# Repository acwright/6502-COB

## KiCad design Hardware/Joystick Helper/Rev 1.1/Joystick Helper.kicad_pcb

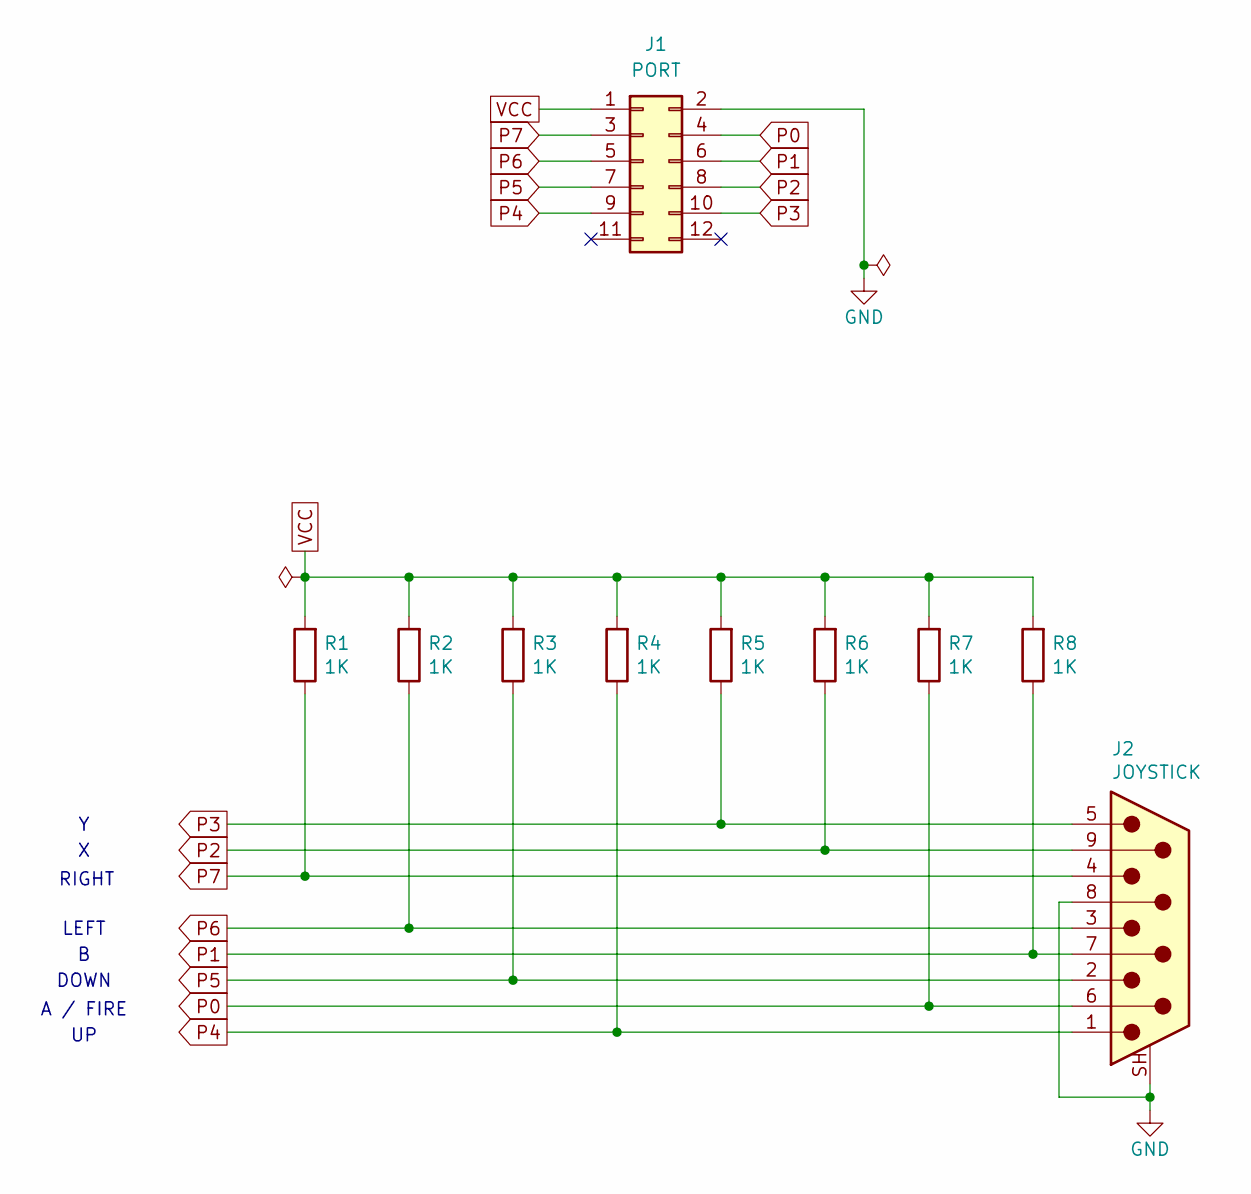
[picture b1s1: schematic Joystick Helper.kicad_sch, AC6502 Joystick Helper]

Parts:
J1: PORT; 6502 GPIO Connector; Digikey 2057-BHR-12-VUA-ND
J2: JOYSTICK; DSUB-9_Pins_Horizontal_P2.77x2.84mm_EdgePinOffset7.70mm_Hou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; Digikey 609-1481-ND
R1, R2, R3, R4, R5, R6, R7, R8: 1K; R_Axial_DIN0204_L3.6mm_D1.6mm_P5.08mm_Horizontal; Digikey 13-MFR-12FTF52-1KCT-ND

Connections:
GND: J1.2, J2.8, J2.SH (PAD)
P0: J1.4, J2.6, R7.1
P1: J1.6, J2.7, R8.1
P2: J1.8, J2.9, R6.1
P3: J1.10, J2.5, R5.1
P4: J1.9, J2.1, R4.1
P5: J1.7, J2.2, R3.1
P6: J1.5, J2.3, R2.1
P7: J1.3, J2.4, R1.1
VCC: J1.1, R1.2, R2.2, R3.2, R4.2, R5.2, R6.2, R7.2, R8.2

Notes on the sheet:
LEFT
DOWN
RIGHT
A / FIRE

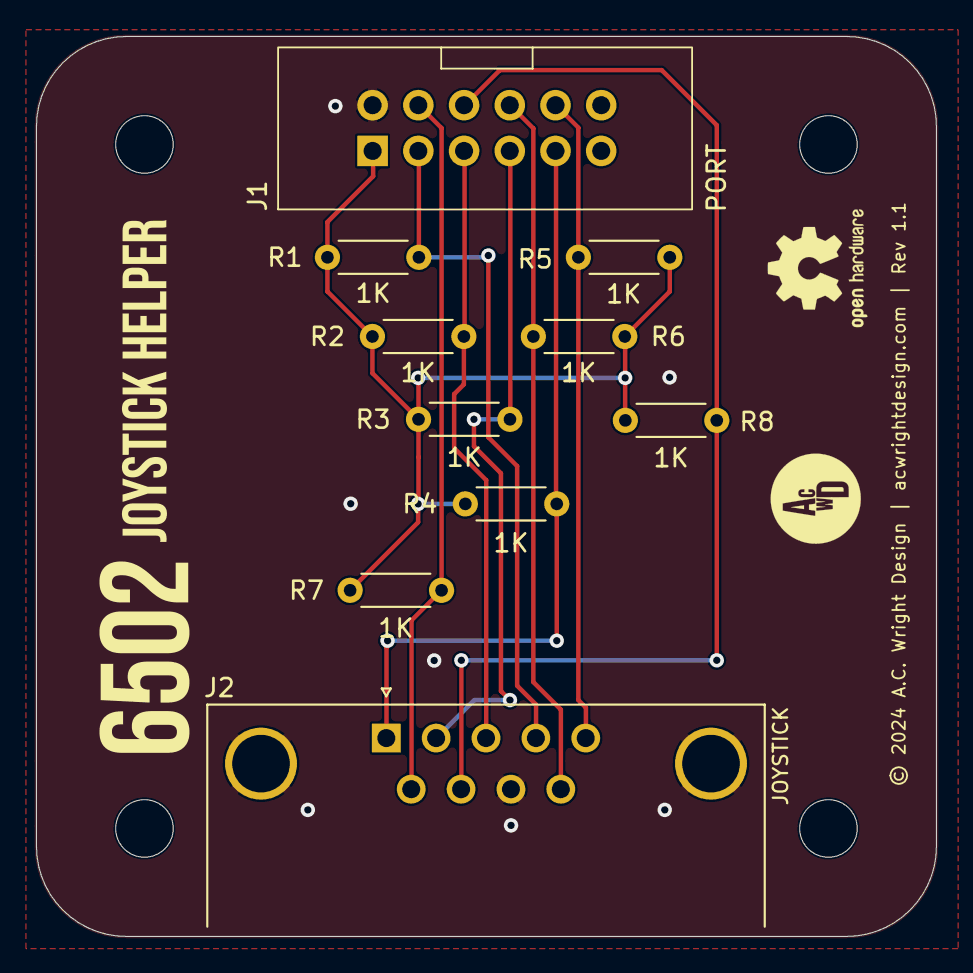
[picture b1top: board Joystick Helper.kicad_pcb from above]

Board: 2 copper layers, 50.0 x 50.0 mm, 14 parts (0 on the bottom side), 10 nets.

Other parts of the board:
H1, H2, H3, H4: MountingHole; MountingHole_3.2mm_M3

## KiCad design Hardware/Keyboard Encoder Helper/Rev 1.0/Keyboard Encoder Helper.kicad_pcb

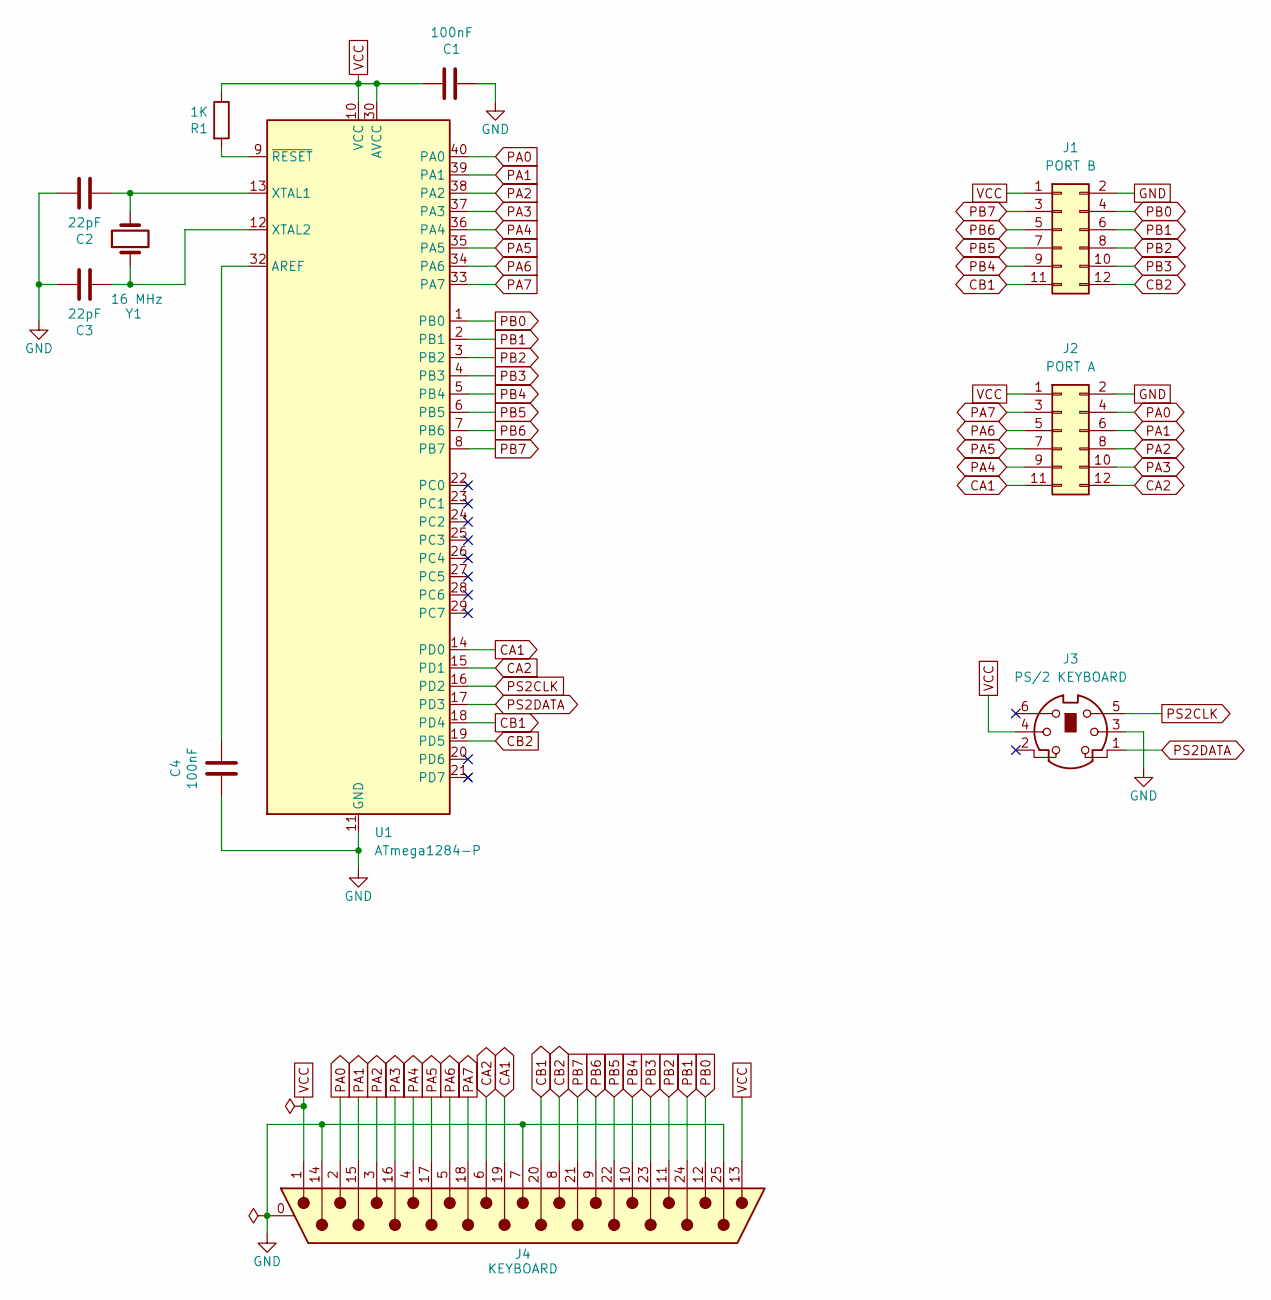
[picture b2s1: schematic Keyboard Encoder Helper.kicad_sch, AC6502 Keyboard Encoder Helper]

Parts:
C1, C4: 100nF; C_Disc_D5.0mm_W2.5mm_P2.50mm; Digikey 478-3187-ND
C2, C3: 22pF; C_Disc_D5.0mm_W2.5mm_P2.50mm; Digikey 478-4846-ND
J1: PORT B; 6502 GPIO Connector; Digikey 2057-BHR-12-VUA-ND
J2: PORT A; 6502 GPIO Connector; Digikey 2057-BHR-12-VUA-ND
J3: PS/2 KEYBOARD; PS2 Jack; Digikey 2092-KMDGX-6S-BS-ND
J4: KEYBOARD; DSUB-25_Pins_Horizontal_P2.77x2.84mm_EdgePinOffset7.70mm_Ho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; Digikey 609-1505-ND
R1: 1K; R_Axial_DIN0204_L3.6mm_D1.6mm_P5.08mm_Horizontal; Digikey 13-MFR-12FTF52-1KCT-ND
U1: ATmega1284-P; DIP-40_W15.24mm_Socket_LongPads; Digikey ATMEGA1284-PU-ND
Y1: 16 MHz; Crystal_HC49-U_Vertical; Digikey X1103-ND

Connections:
CA1: J2.11, J4.19, U1.14 (PD0)
CA2: J2.12, J4.6, U1.15 (PD1)
CB1: J1.11, J4.20, U1.18 (PD4)
CB2: J1.12, J4.8, U1.19 (PD5)
GND: C1.1, C2.2, C3.2, C4.1, J1.2, J2.2, J3.3, J4.0 (PAD), J4.7, J4.14, J4.25, U1.11 (GND), U1.31 (GND)
unnamed: C4.2, U1.32 (AREF)
unnamed: C2.1, U1.13 (XTAL1), Y1.2
unnamed: C3.1, U1.12 (XTAL2), Y1.1
unnamed: R1.2, U1.9 (~RESET)
PA0: J2.4, J4.2, U1.40 (PA0)
PA1: J2.6, J4.15, U1.39 (PA1)
PA2: J2.8, J4.3, U1.38 (PA2)
PA3: J2.10, J4.16, U1.37 (PA3)
PA4: J2.9, J4.4, U1.36 (PA4)
PA5: J2.7, J4.17, U1.35 (PA5)
PA6: J2.5, J4.5, U1.34 (PA6)
PA7: J2.3, J4.18, U1.33 (PA7)
PB0: J1.4, J4.12, U1.1 (PB0)
PB1: J1.6, J4.24, U1.2 (PB1)
PB2: J1.8, J4.11, U1.3 (PB2)
PB3: J1.10, J4.23, U1.4 (PB3)
PB4: J1.9, J4.10, U1.5 (PB4)
PB5: J1.7, J4.22, U1.6 (PB5)
PB6: J1.5, J4.9, U1.7 (PB6)
PB7: J1.3, J4.21, U1.8 (PB7)
PS2CLK: J3.5, U1.16 (PD2)
PS2DATA: J3.1, U1.17 (PD3)
VCC: C1.2, J1.1, J2.1, J3.4, J4.1, J4.13, R1.1, U1.10 (VCC), U1.30 (AVCC)

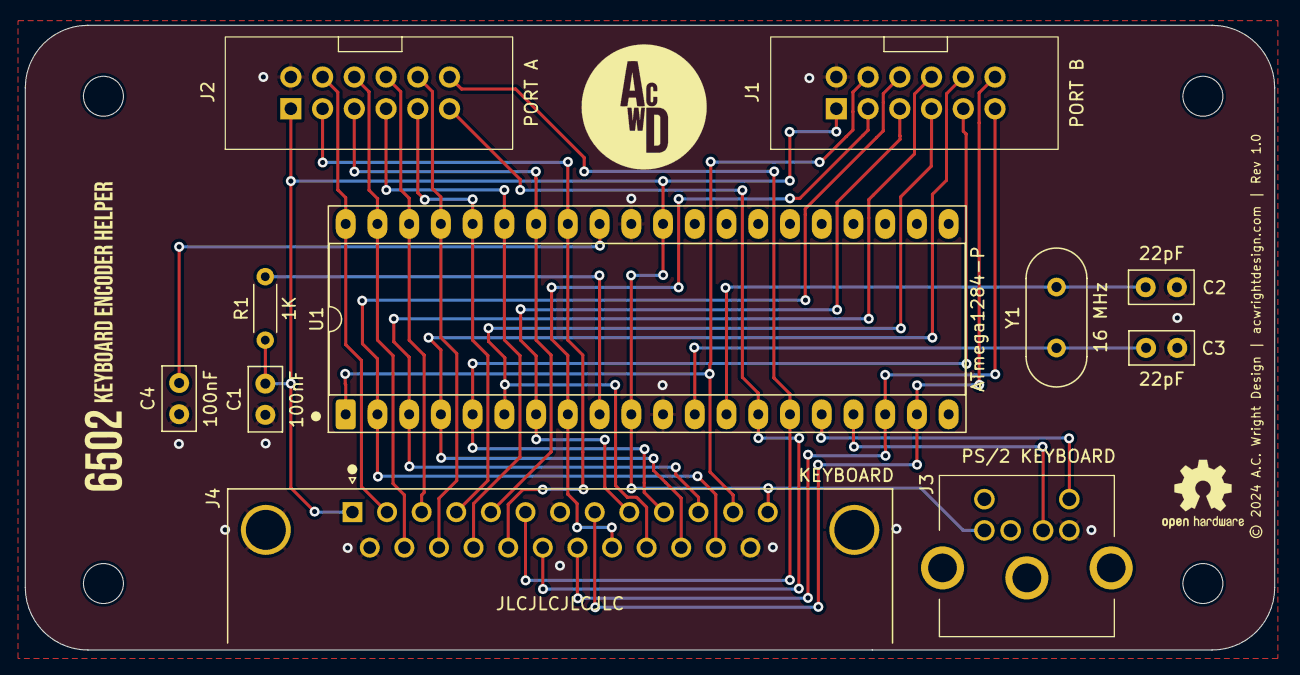
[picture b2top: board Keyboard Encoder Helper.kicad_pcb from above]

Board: 2 copper layers, 100.0 x 50.0 mm, 15 parts (0 on the bottom side), 28 nets.

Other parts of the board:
H1, H2, H3, H4: MountingHole; MountingHole_3.2mm_M3

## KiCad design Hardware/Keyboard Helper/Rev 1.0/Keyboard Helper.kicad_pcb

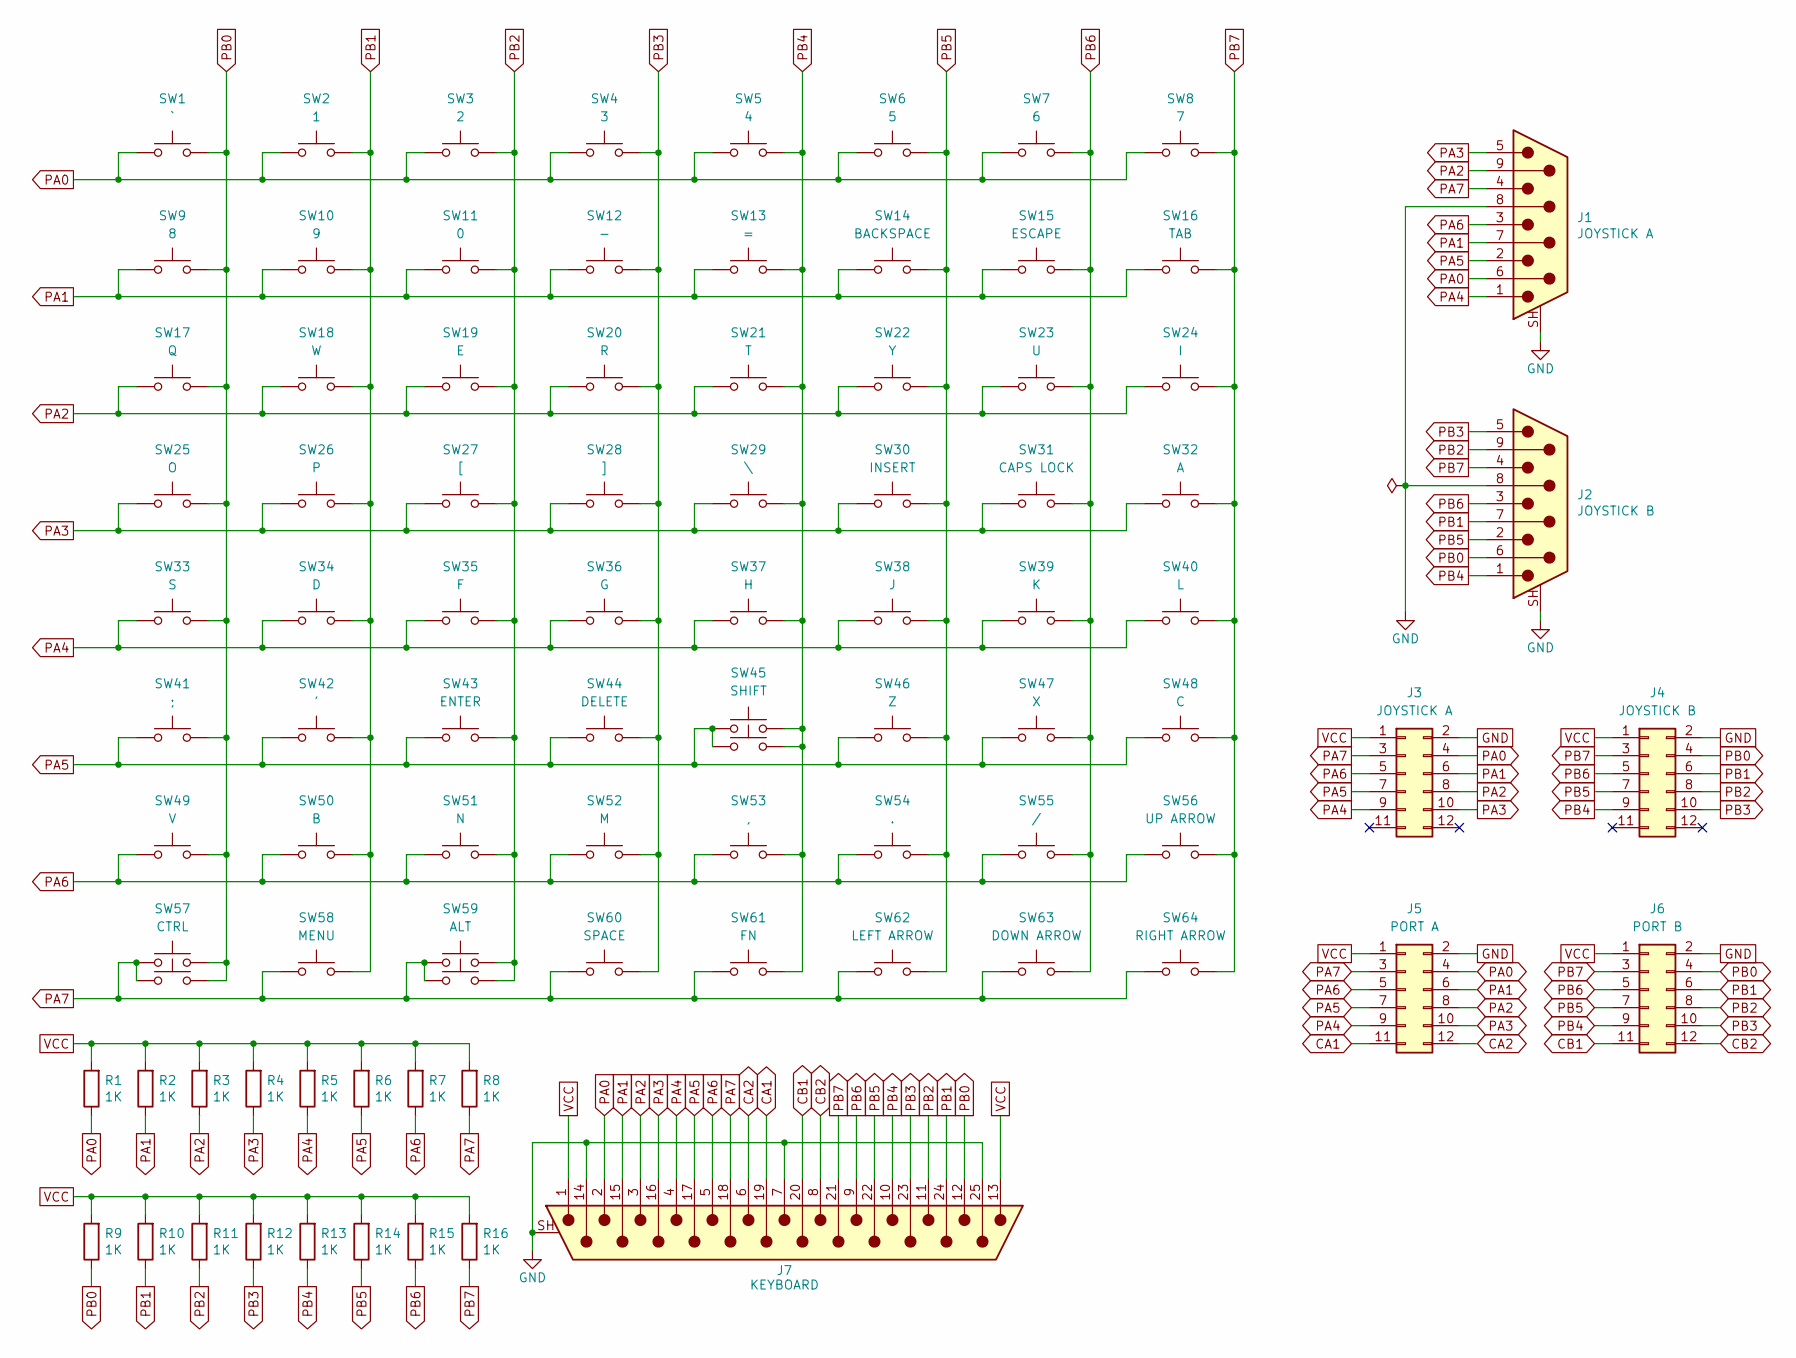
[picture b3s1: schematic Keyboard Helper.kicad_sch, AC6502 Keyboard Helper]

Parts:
J1: JOYSTICK A; DSUB-9_Pins_Horizontal_P2.77x2.84mm_EdgePinOffset7.70mm_Hou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; Digikey 609-1481-ND
J2: JOYSTICK B; DSUB-9_Pins_Horizontal_P2.77x2.84mm_EdgePinOffset7.70mm_Hou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; Digikey 609-1481-ND
J3: JOYSTICK A; 6502 GPIO Connector; Digikey 2057-BHR-12-VUA-ND
J4: JOYSTICK B; 6502 GPIO Connector; Digikey 2057-BHR-12-VUA-ND
J5: PORT A; 6502 GPIO Connector; Digikey 2057-BHR-12-VUA-ND
J6: PORT B; 6502 GPIO Connector; Digikey 2057-BHR-12-VUA-ND
J7: KEYBOARD; DSUB-25_Pins_Horizontal_P2.77x2.84mm_EdgePinOffset7.70mm_Ho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; Digikey 609-1505-ND
R1, R2, R3, R4, R5, R6, R7, R8, R9, R10, R11, R12, R13, R14, R15, R16: 1K; R_Axial_DIN0204_L3.6mm_D1.6mm_P5.08mm_Horizontal; Digikey 13-MFR-12FTF52-1KCT-ND
SW1: `; SW_Cherry_MX_1.00u_PCB; Digikey 1644-MX2A-E1NA-ND
SW2: 1; SW_Cherry_MX_1.00u_PCB; Digikey 1644-MX2A-E1NA-ND
SW3: 2; SW_Cherry_MX_1.00u_PCB; Digikey 1644-MX2A-E1NA-ND
SW4: 3; SW_Cherry_MX_1.00u_PCB; Digikey 1644-MX2A-E1NA-ND
SW5: 4; SW_Cherry_MX_1.00u_PCB; Digikey 1644-MX2A-E1NA-ND
SW6: 5; SW_Cherry_MX_1.00u_PCB; Digikey 1644-MX2A-E1NA-ND
SW7: 6; SW_Cherry_MX_1.00u_PCB; Digikey 1644-MX2A-E1NA-ND
SW8: 7; SW_Cherry_MX_1.00u_PCB; Digikey 1644-MX2A-E1NA-ND
SW9: 8; SW_Cherry_MX_1.00u_PCB; Digikey 1644-MX2A-E1NA-ND
SW10: 9; SW_Cherry_MX_1.00u_PCB; Digikey 1644-MX2A-E1NA-ND
SW11: 0; SW_Cherry_MX_1.00u_PCB; Digikey 1644-MX2A-E1NA-ND
SW12: -; SW_Cherry_MX_1.00u_PCB; Digikey 1644-MX2A-E1NA-ND
SW13: =; SW_Cherry_MX_1.00u_PCB; Digikey 1644-MX2A-E1NA-ND
SW14: BACKSPACE; SW_Cherry_MX_2.00u_PCB; Digikey 1644-MX2A-E1NA-ND
SW15: ESCAPE; SW_Cherry_MX_1.00u_PCB; Digikey 1644-MX2A-E1NA-ND
SW16: TAB; SW_Cherry_MX_1.50u_PCB; Digikey 1644-MX2A-E1NA-ND
SW17: Q; SW_Cherry_MX_1.00u_PCB; Digikey 1644-MX2A-E1NA-ND
SW18: W; SW_Cherry_MX_1.00u_PCB; Digikey 1644-MX2A-E1NA-ND
SW19: E; SW_Cherry_MX_1.00u_PCB; Digikey 1644-MX2A-E1NA-ND
SW20: R; SW_Cherry_MX_1.00u_PCB; Digikey 1644-MX2A-E1NA-ND
SW21: T; SW_Cherry_MX_1.00u_PCB; Digikey 1644-MX2A-E1NA-ND
SW22: Y; SW_Cherry_MX_1.00u_PCB; Digikey 1644-MX2A-E1NA-ND
SW23: U; SW_Cherry_MX_1.00u_PCB; Digikey 1644-MX2A-E1NA-ND
SW24: I; SW_Cherry_MX_1.00u_PCB; Digikey 1644-MX2A-E1NA-ND
SW25: O; SW_Cherry_MX_1.00u_PCB; Digikey 1644-MX2A-E1NA-ND
SW26: P; SW_Cherry_MX_1.00u_PCB; Digikey 1644-MX2A-E1NA-ND
SW27: [; SW_Cherry_MX_1.00u_PCB; Digikey 1644-MX2A-E1NA-ND
SW28: ]; SW_Cherry_MX_1.00u_PCB; Digikey 1644-MX2A-E1NA-ND
SW29: \; SW_Cherry_MX_1.50u_PCB; Digikey 1644-MX2A-E1NA-ND
SW30: INSERT; SW_Cherry_MX_1.00u_PCB; Digikey 1644-MX2A-E1NA-ND
SW31: CAPS LOCK; SW_Cherry_MX_1.75u_PCB; Digikey 1644-MX2A-E1NA-ND
SW32: A; SW_Cherry_MX_1.00u_PCB; Digikey 1644-MX2A-E1NA-ND
SW33: S; SW_Cherry_MX_1.00u_PCB; Digikey 1644-MX2A-E1NA-ND
SW34: D; SW_Cherry_MX_1.00u_PCB; Digikey 1644-MX2A-E1NA-ND
SW35: F; SW_Cherry_MX_1.00u_PCB; Digikey 1644-MX2A-E1NA-ND
SW36: G; SW_Cherry_MX_1.00u_PCB; Digikey 1644-MX2A-E1NA-ND
SW37: H; SW_Cherry_MX_1.00u_PCB; Digikey 1644-MX2A-E1NA-ND
SW38: J; SW_Cherry_MX_1.00u_PCB; Digikey 1644-MX2A-E1NA-ND
SW39: K; SW_Cherry_MX_1.00u_PCB; Digikey 1644-MX2A-E1NA-ND
SW40: L; SW_Cherry_MX_1.00u_PCB; Digikey 1644-MX2A-E1NA-ND
SW41: ;; SW_Cherry_MX_1.00u_PCB; Digikey 1644-MX2A-E1NA-ND
SW42: '; SW_Cherry_MX_1.00u_PCB; Digikey 1644-MX2A-E1NA-ND
SW43: ENTER; SW_Cherry_MX_2.25u_PCB; Digikey 1644-MX2A-E1NA-ND
SW44: DELETE; SW_Cherry_MX_1.00u_PCB; Digikey 1644-MX2A-E1NA-ND
SW45: SHIFT; SW_Cherry_MX_2.25u_PCB; Digikey 1644-MX2A-E1NA-ND
SW46: Z; SW_Cherry_MX_1.00u_PCB; Digikey 1644-MX2A-E1NA-ND
SW47: X; SW_Cherry_MX_1.00u_PCB; Digikey 1644-MX2A-E1NA-ND
SW48: C; SW_Cherry_MX_1.00u_PCB; Digikey 1644-MX2A-E1NA-ND
SW49: V; SW_Cherry_MX_1.00u_PCB; Digikey 1644-MX2A-E1NA-ND
SW50: B; SW_Cherry_MX_1.00u_PCB; Digikey 1644-MX2A-E1NA-ND
SW51: N; SW_Cherry_MX_1.00u_PCB; Digikey 1644-MX2A-E1NA-ND
SW52: M; SW_Cherry_MX_1.00u_PCB; Digikey 1644-MX2A-E1NA-ND
SW53: ,; SW_Cherry_MX_1.00u_PCB; Digikey 1644-MX2A-E1NA-ND
SW54: .; SW_Cherry_MX_1.00u_PCB; Digikey 1644-MX2A-E1NA-ND
SW55: /; SW_Cherry_MX_1.00u_PCB; Digikey 1644-MX2A-E1NA-ND
SW56: UP ARROW; SW_Cherry_MX_1.00u_PCB; Digikey 1644-MX2A-E1NA-ND
SW57: CTRL; SW_Cherry_MX_1.25u_PCB; Digikey 1644-MX2A-E1NA-ND
SW58: MENU; SW_Cherry_MX_1.00u_PCB; Digikey 1644-MX2A-E1NA-ND
SW59: ALT; SW_Cherry_MX_1.25u_PCB; Digikey 1644-MX2A-E1NA-ND
SW60: SPACE; SW_Cherry_MX_6.25u_PCB; Digikey 1644-MX2A-E1NA-ND
SW61: FN; SW_Cherry_MX_1.25u_PCB; Digikey 1644-MX2A-E1NA-ND
SW62: LEFT ARROW; SW_Cherry_MX_1.00u_PCB; Digikey 1644-MX2A-E1NA-ND
SW63: DOWN ARROW; SW_Cherry_MX_1.00u_PCB; Digikey 1644-MX2A-E1NA-ND
SW64: RIGHT ARROW; SW_Cherry_MX_1.00u_PCB; Digikey 1644-MX2A-E1NA-ND
SW65: R SHIFT; SW_Cherry_MX_2.25u_PCB; Digikey 1644-MX2A-E1NA-ND
SW66: R ALT; SW_Cherry_MX_1.25u_PCB; Digikey 1644-MX2A-E1NA-ND
SW67: R CTRL; SW_Cherry_MX_1.25u_PCB; Digikey 1644-MX2A-E1NA-ND

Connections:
CA1: J5.11, J7.19
CA2: J5.12, J7.6
CB1: J6.11, J7.20
CB2: J6.12, J7.8
GND: J1.8, J1.SH (PAD), J2.8, J2.SH (PAD), J3.2, J4.2, J5.2, J6.2, J7.7, J7.14, J7.25, J7.SH (PAD)
PA0: J1.6, J3.4, J5.4, J7.2, R1.1, SW1.1, SW2.1, SW3.1, SW4.1, SW5.1, SW6.1, SW7.1, SW8.1
PA1: J1.7, J3.6, J5.6, J7.15, R2.1, SW9.1, SW10.1, SW11.1, SW12.1, SW13.1, SW14.1, SW15.1, SW16.1
PA2: J1.9, J3.8, J5.8, J7.3, R3.1, SW17.1, SW18.1, SW19.1, SW20.1, SW21.1, SW22.1, SW23.1, SW24.1
PA3: J1.5, J3.10, J5.10, J7.16, R4.1, SW25.1, SW26.1, SW27.1, SW28.1, SW29.1, SW30.1, SW31.1, SW32.1
PA4: J1.1, J3.9, J5.9, J7.4, R5.1, SW33.1, SW34.1, SW35.1, SW36.1, SW37.1, SW38.1, SW39.1, SW40.1
PA5: J1.2, J3.7, J5.7, J7.17, R6.1, SW41.1, SW42.1, SW43.1, SW44.1, SW45.1, SW46.1, SW47.1, SW48.1, SW65.1
PA6: J1.3, J3.5, J5.5, J7.5, R7.1, SW49.1, SW50.1, SW51.1, SW52.1, SW53.1, SW54.1, SW55.1, SW56.1
PA7: J1.4, J3.3, J5.3, J7.18, R8.1, SW57.1, SW58.1, SW59.1, SW60.1, SW61.1, SW62.1, SW63.1, SW64.1, SW66.1, SW67.1
PB0: J2.6, J4.4, J6.4, J7.12, R9.1, SW1.2, SW9.2, SW17.2, SW25.2, SW33.2, SW41.2, SW49.2, SW57.2, SW67.2
PB1: J2.7, J4.6, J6.6, J7.24, R10.1, SW2.2, SW10.2, SW18.2, SW26.2, SW34.2, SW42.2, SW50.2, SW58.2
PB2: J2.9, J4.8, J6.8, J7.11, R11.1, SW3.2, SW11.2, SW19.2, SW27.2, SW35.2, SW43.2, SW51.2, SW59.2, SW66.2
PB3: J2.5, J4.10, J6.10, J7.23, R12.1, SW4.2, SW12.2, SW20.2, SW28.2, SW36.2, SW44.2, SW52.2, SW60.2
PB4: J2.1, J4.9, J6.9, J7.10, R13.1, SW5.2, SW13.2, SW21.2, SW29.2, SW37.2, SW45.2, SW53.2, SW61.2, SW65.2
PB5: J2.2, J4.7, J6.7, J7.22, R14.1, SW6.2, SW14.2, SW22.2, SW30.2, SW38.2, SW46.2, SW54.2, SW62.2
PB6: J2.3, J4.5, J6.5, J7.9, R15.1, SW7.2, SW15.2, SW23.2, SW31.2, SW39.2, SW47.2, SW55.2, SW63.2
PB7: J2.4, J4.3, J6.3, J7.21, R16.1, SW8.2, SW16.2, SW24.2, SW32.2, SW40.2, SW48.2, SW56.2, SW64.2
VCC: J3.1, J4.1, J5.1, J6.1, J7.1, J7.13, R1.2, R2.2, R3.2, R4.2, R5.2, R6.2, R7.2, R8.2, R9.2, R10.2, R11.2, R12.2, R13.2, R14.2, R15.2, R16.2

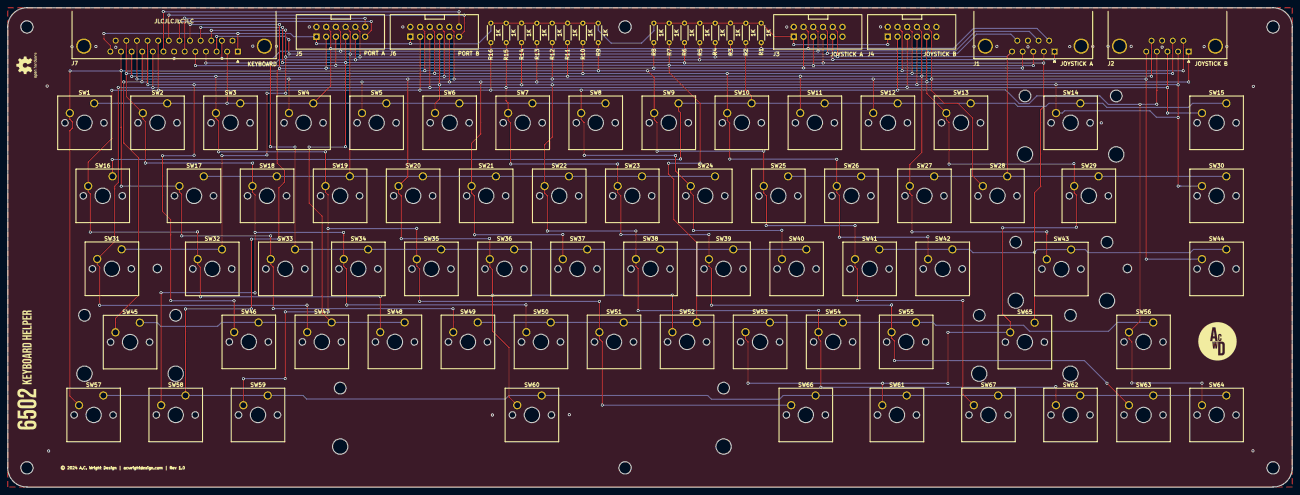
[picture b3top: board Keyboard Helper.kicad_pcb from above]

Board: 2 copper layers, 335.0 x 125.0 mm, 98 parts (0 on the bottom side), 22 nets.

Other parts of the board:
H1, H2, H2#2, H2#3, H3#3, H4: MountingHole; MountingHole_3.2mm_M3
H3, H3#2: MountingHole; MountingHole_2.2mm_M2

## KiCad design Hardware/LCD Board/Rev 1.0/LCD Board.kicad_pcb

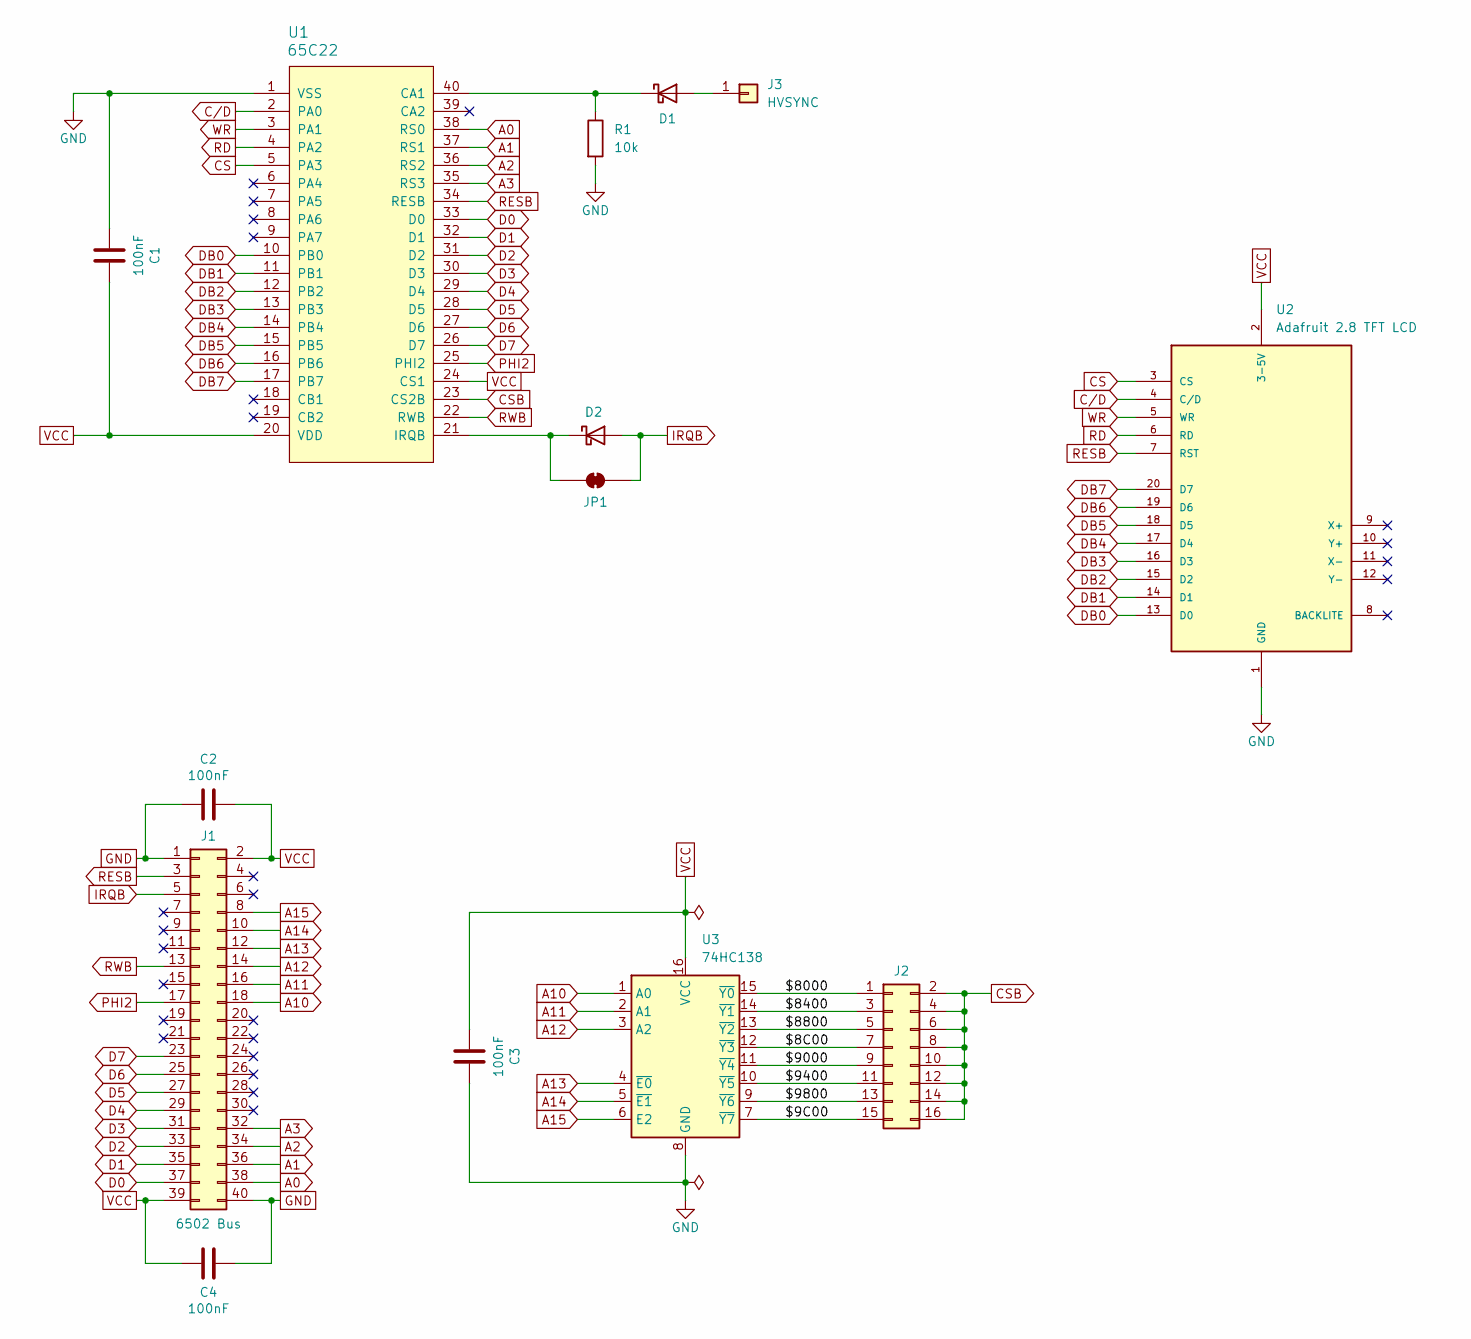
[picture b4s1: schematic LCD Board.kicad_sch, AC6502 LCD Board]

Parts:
C1, C2, C3, C4: 100nF; C_Disc_D5.0mm_W2.5mm_P2.50mm; Digikey 478-3187-ND
D1, D2: BAT85; D_DO-35_SOD27_P7.62mm_Horizontal; Digikey BAT85SCT-ND
J1: 6502 Bus; 6502 Bus Connector; Digikey 732-5401-ND
J2: Conn_02x08_Odd_Even; PinHeader_2x08_P2.54mm_Vertical; Digikey S2011EC-40-ND
J3: HVSYNC; PinHeader_1x01_P2.54mm_Vertical; Digikey S1011EC-40-ND
JP1: SolderJumper_2_Bridged; SolderJumper-2_P1.3mm_Bridged_RoundedPad1.0x1.5mm
R1: 10k; R_Axial_DIN0204_L3.6mm_D1.6mm_P5.08mm_Horizontal; Digikey 13-MFR-12FTF52-10KCT-ND
U1: 65C22; DIP-40_W15.24mm_Socket_LongPads; Mouser 955-W65C22N6TPG-14
U2: Adafruit 2.8 TFT LCD
U3: 74HC138; DIP-16_W7.62mm_Socket_LongPads; Digikey 296-1575-5-ND

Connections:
/$8C00: J2.7, U3.12 (~Y3)
/$9C00: J2.15, U3.7 (~Y7)
/$8000: J2.1, U3.15 (~Y0)
/$8400: J2.3, U3.14 (~Y1)
/$8800: J2.5, U3.13 (~Y2)
/$9000: J2.9, U3.11 (~Y4)
/$9400: J2.11, U3.10 (~Y5)
/$9800: J2.13, U3.9 (~Y6)
A0: J1.38, U1.38 (RS0)
A1: J1.36, U1.37 (RS1)
A2: J1.34, U1.36 (RS2)
A3: J1.32, U1.35 (RS3)
A10: J1.18, U3.1 (A0)
A11: J1.16, U3.2 (A1)
A12: J1.14, U3.3 (A2)
A13: J1.12, U3.4 (~E0)
A14: J1.10, U3.5 (~E1)
A15: J1.8, U3.6 (E2)
CS: U1.5 (PA3), U2.3 (CS)
CSB: J2.2, J2.4, J2.6, J2.8, J2.10, J2.12, J2.14, J2.16, U1.23 (CS2B)
C/D: U1.2 (PA0), U2.4 (C/D)
D0: J1.37, U1.33 (D0)
D1: J1.35, U1.32 (D1)
D2: J1.33, U1.31 (D2)
D3: J1.31, U1.30 (D3)
D4: J1.29, U1.29 (D4)
D5: J1.27, U1.28 (D5)
D6: J1.25, U1.27 (D6)
D7: J1.23, U1.26 (D7)
DB0: U1.10 (PB0), U2.13 (D0)
DB1: U1.11 (PB1), U2.14 (D1)
DB2: U1.12 (PB2), U2.15 (D2)
DB3: U1.13 (PB3), U2.16 (D3)
DB4: U1.14 (PB4), U2.17 (D4)
DB5: U1.15 (PB5), U2.18 (D5)
DB6: U1.16 (PB6), U2.19 (D6)
DB7: U1.17 (PB7), U2.20 (D7)
GND: C1.1, C2.2, C3.2, C4.1, J1.1, J1.40, R1.2, U1.1 (VSS), U2.1 (GND), U3.8 (GND)
IRQB: D2.2 (A), J1.5, JP1.2 (B)
unnamed: D1.2 (A), J3.1
unnamed: D1.1 (K), R1.1, U1.40 (CA1)
unnamed: D2.1 (K), JP1.1 (A), U1.21 (IRQB)
PHI2: J1.17, U1.25 (PHI2)
RD: U1.4 (PA2), U2.6 (RD)
RESB: J1.3, U1.34 (RESB), U2.7 (RST)
RWB: J1.13, U1.22 (RWB)
VCC: C1.2, C2.1, C3.1, C4.2, J1.2, J1.39, U1.20 (VDD), U1.24 (CS1), U2.2 (3-5V), U3.16 (VCC)
WR: U1.3 (PA1), U2.5 (WR)

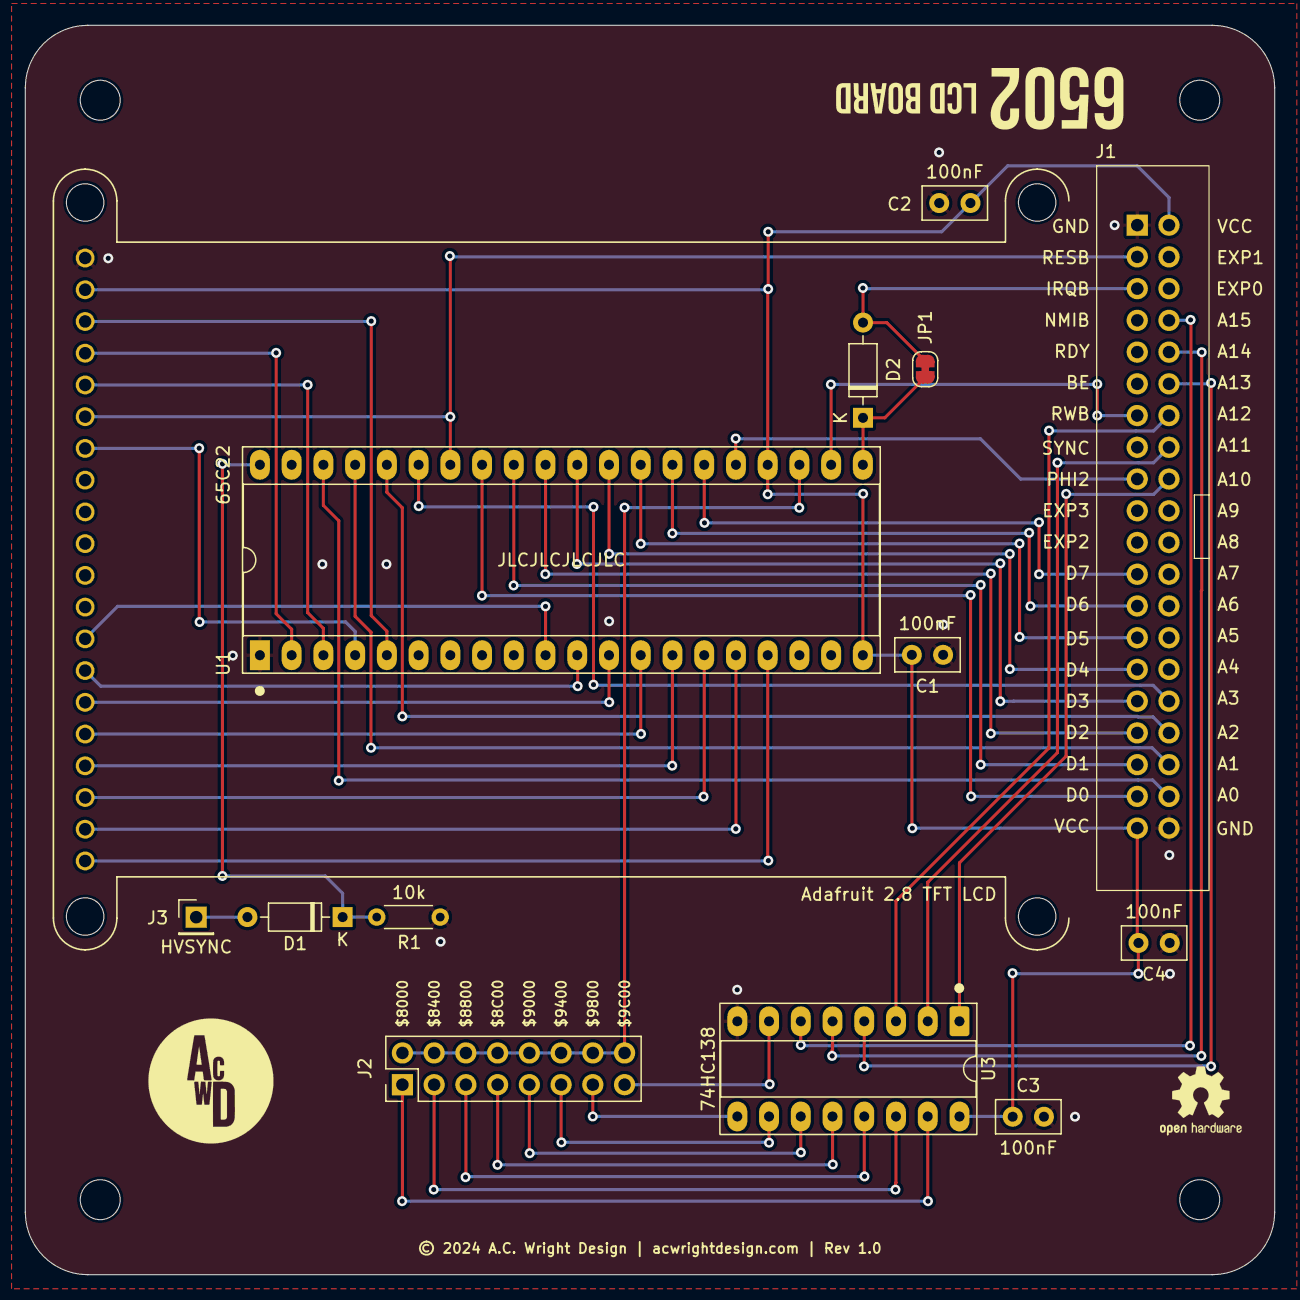
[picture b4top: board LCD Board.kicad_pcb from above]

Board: 2 copper layers, 100.0 x 100.0 mm, 18 parts (0 on the bottom side), 48 nets.

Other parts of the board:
H1, H2, H3, H4: MountingHole; MountingHole_3.2mm_M3

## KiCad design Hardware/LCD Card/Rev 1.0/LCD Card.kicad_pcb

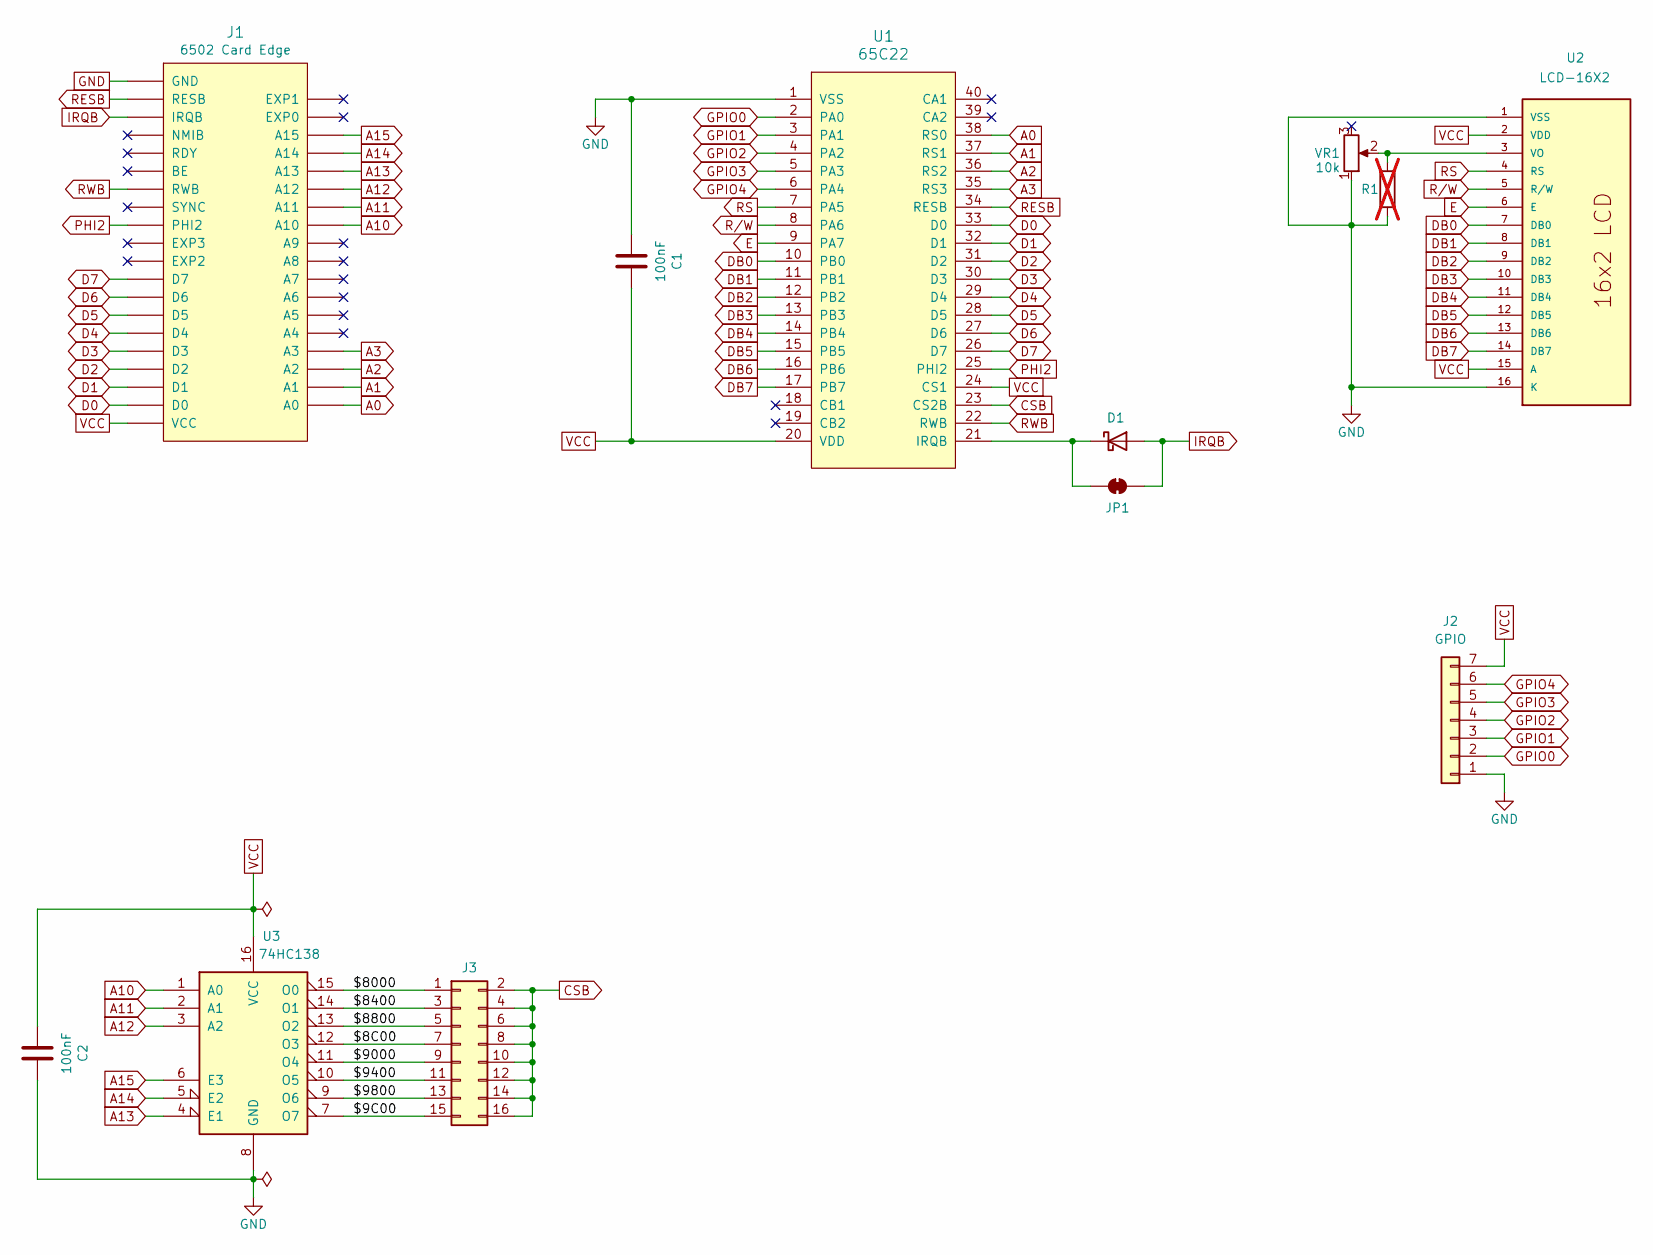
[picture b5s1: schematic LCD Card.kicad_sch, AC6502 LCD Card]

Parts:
C1, C2: 100nF; C_0805_2012Metric; LCSC C49678
D1: BAT85; D_DO-35_SOD27_P7.62mm_Horizontal; Digikey BAT85SCT-ND
J1: 6502 Card Edge
J2: GPIO; PinHeader_1x07_P2.54mm_Horizontal; Digikey 2057-PH1RB-07-UA-ND
J3: Conn_02x08_Odd_Even; PinHeader_2x08_P2.54mm_Vertical; Digikey S2011EC-40-ND
JP1: SolderJumper_2_Bridged; SolderJumper-2_P1.3mm_Bridged_RoundedPad1.0x1.5mm
R1: DNP: parallel with VR1 to make ~10 k; R_Axial_DIN0204_L3.6mm_D1.6mm_P5.08mm_Horizontal; not fitted
U1: 65C22; DIP-40_W15.24mm_Socket_LongPads; Mouser 955-W65C22N6TPG-14
U2: LCD-16X2
U3: 74HC138; SOIC-16_3.9x9.9mm_P1.27mm; LCSC C5602
VR1: 10k; Trimmer 3386F; Digikey 3386F-103LF-ND

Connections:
/$8C00: J3.7, U3.12 (O3)
/$9C00: J3.15, U3.7 (O7)
/$8000: J3.1, U3.15 (O0)
/$8400: J3.3, U3.14 (O1)
/$8800: J3.5, U3.13 (O2)
/$9000: J3.9, U3.11 (O4)
/$9400: J3.11, U3.10 (O5)
/$9800: J3.13, U3.9 (O6)
A0: J1.A0, U1.38 (RS0)
A1: J1.A1, U1.37 (RS1)
A2: J1.A2, U1.36 (RS2)
A3: J1.A3, U1.35 (RS3)
A10: J1.A10, U3.1 (A0)
A11: J1.A11, U3.2 (A1)
A12: J1.A12, U3.3 (A2)
A13: J1.A13, U3.4 (E1)
A14: J1.A14, U3.5 (E2)
A15: J1.A15, U3.6 (E3)
CSB: J3.2, J3.4, J3.6, J3.8, J3.10, J3.12, J3.14, J3.16, U1.23 (CS2B)
D0: J1.D0, U1.33 (D0)
D1: J1.D1, U1.32 (D1)
D2: J1.D2, U1.31 (D2)
D3: J1.D3, U1.30 (D3)
D4: J1.D4, U1.29 (D4)
D5: J1.D5, U1.28 (D5)
D6: J1.D6, U1.27 (D6)
D7: J1.D7, U1.26 (D7)
DB0: U1.10 (PB0), U2.7 (DB0)
DB1: U1.11 (PB1), U2.8 (DB1)
DB2: U1.12 (PB2), U2.9 (DB2)
DB3: U1.13 (PB3), U2.10 (DB3)
DB4: U1.14 (PB4), U2.11 (DB4)
DB5: U1.15 (PB5), U2.12 (DB5)
DB6: U1.16 (PB6), U2.13 (DB6)
DB7: U1.17 (PB7), U2.14 (DB7)
E: U1.9 (PA7), U2.6 (E)
GND: C1.1, C2.2, J1.GND, J2.1, R1.2, U1.1 (VSS), U2.1 (VSS), U2.16 (K), U3.8 (GND), VR1.1
GPIO0: J2.2, U1.2 (PA0)
GPIO1: J2.3, U1.3 (PA1)
GPIO2: J2.4, U1.4 (PA2)
GPIO3: J2.5, U1.5 (PA3)
GPIO4: J2.6, U1.6 (PA4)
IRQB: D1.2 (A), J1.IRQB, JP1.2 (B)
unnamed: D1.1 (K), JP1.1 (A), U1.21 (IRQB)
unnamed: R1.1, U2.3 (VO), VR1.2
PHI2: J1.PHI2, U1.25 (PHI2)
RESB: J1.RESB, U1.34 (RESB)
RS: U1.7 (PA5), U2.4 (RS)
RWB: J1.RWB, U1.22 (RWB)
R/W: U1.8 (PA6), U2.5 (R/W)
VCC: C1.2, C2.1, J1.VCC, J2.7, U1.20 (VDD), U1.24 (CS1), U2.2 (VDD), U2.15 (A), U3.16 (VCC)

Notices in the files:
Hardware/Joystick Helper/Rev 1.1/Joystick Helper.kicad_pcb:
© 2024 A.C. Wright Design | acwrightdesign.com | Rev 1.1
Hardware/Keyboard Encoder Helper/Rev 1.0/Keyboard Encoder Helper.kicad_pcb:
© 2024 A.C. Wright Design | acwrightdesign.com | Rev 1.0
